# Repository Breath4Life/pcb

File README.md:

# Electronic circuit description

In this repository you will find the design files for hardware electronic design for the Breath4Life project.
Supported CAD software:
- Eagle

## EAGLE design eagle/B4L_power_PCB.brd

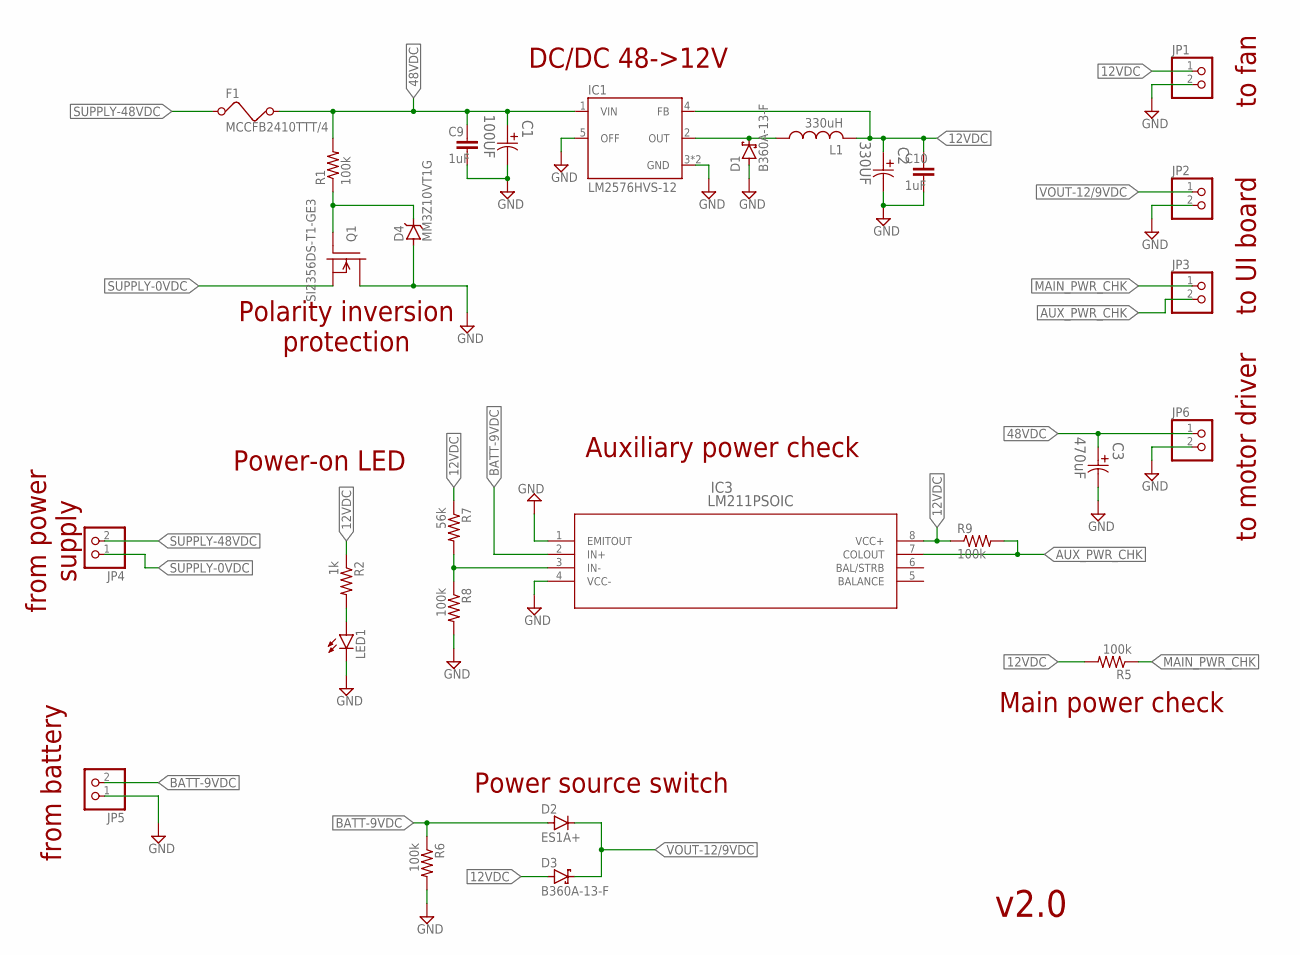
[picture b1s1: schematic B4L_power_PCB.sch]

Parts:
C1: 100UF; CAPAE1900X2200N
C2: 330UF; CAPAE830X1050N
C3: 470uF; CAPAE1900X1700N
C9: 1uF; C1206
C10: 1uF; C0603
D1, D3: B360A-13-F; DO214AC
D2: ES1A+; DO214AC
D4: MM3Z10VT1G; SOD323
F1: MCCFB2410TTT/4
IC1: LM2576HVS-12; TO263-5
IC3: LM211PSOIC; SO08
JP1, JP2, JP3, JP4, JP5, JP6: PINHD-1X2; 1X02
L1: 330uH; SRR1280A-331K
LED1: LED3MM
Q1: SI2356DS-T1-GE3; SOT23
R1, R5, R6, R8, R9: 100k; R0603
R2: 1k; R0603
R7: 56k; R0603

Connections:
12VDC: C2.1, C10.1, D3.A, IC1.4 (FB), IC3.8 (VCC+), JP1.1, L1.P$2 (2), R2.1, R5.2, R7.1, R9.1
48VDC: C1.1, C3.1, C9.1, F1.P$2 (2), IC1.1 (VIN), JP6.1, R1.2
AUX_PWR_CHK: IC3.7 (COLOUT), JP3.2, R9.2
BATT-9VDC: D2.A, IC3.2 (IN+), JP5.2, R6.1
GND: C1.2, C2.2, C3.2, C9.2, C10.2, D1.A, D4.2 (A), IC1.3 (GND), IC1.5 (OFF), IC1.6 (GND), IC3.1 (EMITOUT), IC3.4 (VCC-), JP1.2, JP2.2, JP5.1, JP6.2, LED1.K (C), Q1.3 (D), R6.2, R8.2
MAIN_PWR_CHK: JP3.1, R5.1
unnamed: D1.C, IC1.2 (OUT), L1.P$1 (1)
unnamed: D4.1 (C), Q1.1 (G), R1.1
unnamed: LED1.A, R2.2
unnamed: IC3.3 (IN-), R7.2, R8.1
SUPPLY-0VDC: JP4.1, Q1.2 (S)
SUPPLY-48VDC: F1.P$1 (1), JP4.2
VOUT-12/9VDC: D2.C, D3.C, JP2.1

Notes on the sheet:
v2.0
DC/DC 48->12V
Polarity inversion protection
Power source switch
to fan
Main power check
from battery
from power supply
Auxiliary power check
to UI board
to motor driver
Power-on LED

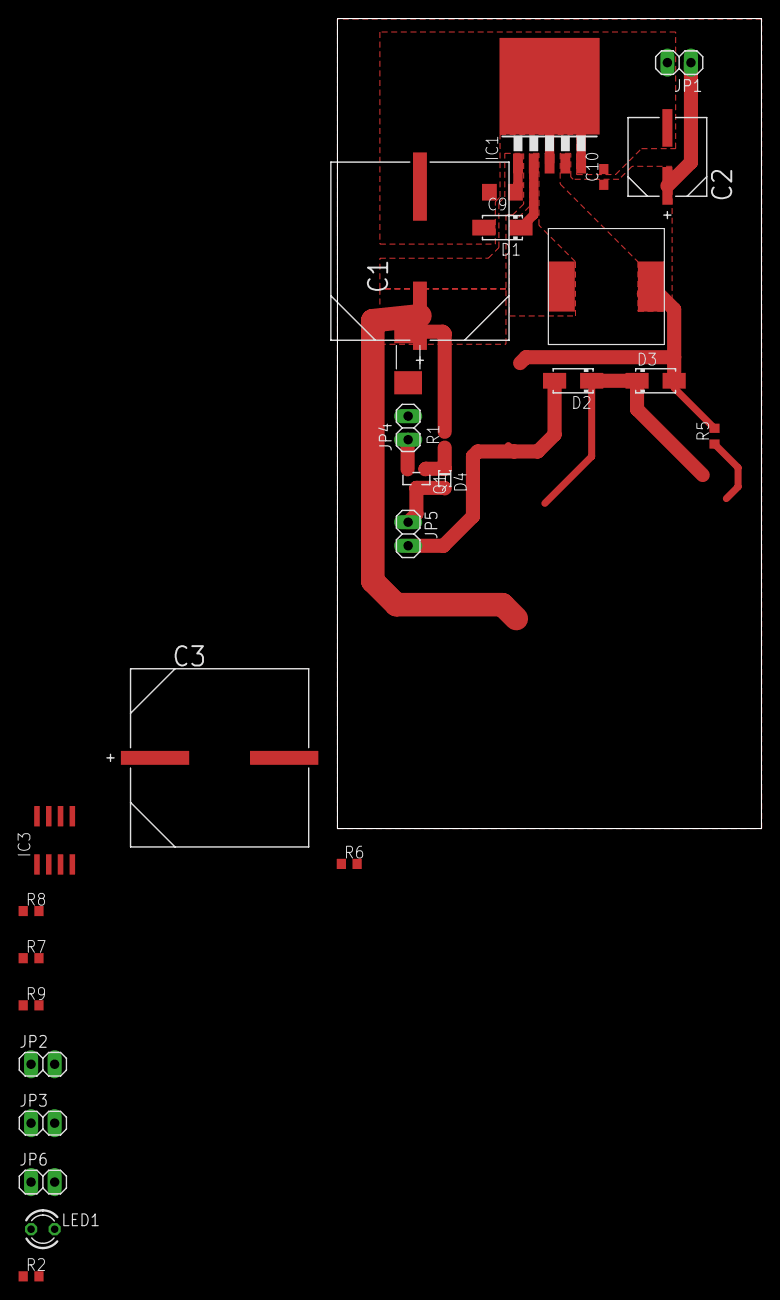
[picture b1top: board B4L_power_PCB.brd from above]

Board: 2 copper layers, 45.7 x 87.3 mm, 28 parts (0 on the bottom side), 13 nets.

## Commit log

2020-03-30 Add gitignore
2020-03-30 Add power board
2020-03-30 Add UI board (pin mapping not OK)
2020-03-31 Update UI, correct pin mapping
2020-03-31 Duplicate UART (for TX/RX on arduino)
2020-04-03 start v2 PCB design
2020-04-03 finish initial routing
2020-04-15 Power board update to 48V
2020-04-16 Update of LCD connectivity and capacitor values (near buttons)
2020-04-16 [UI board] Update of LEDs and resistors
2020-04-16 Create power board BOM
2020-04-16 [UI board] Addition of ACK button
2020-04-16 [UI board] Update of Arduino pin header connectivity
2020-04-16 Add schematic pdf
2020-04-16 Update PCB power for 48V supply
2020-04-19 [UI board] Update of buzzer driving circuit
2020-04-22 [UI board] Update of PDF version of the schematic
2020-04-22 Add motor, lim switch & flow sensor connexions to UI board
2020-04-22 update TODO
2020-04-22 Add value for capacitors
2020-04-23 [UI board] Correction of RBUZM resistor value
2020-04-23 add UI netlist
2020-04-28 [UI board] Correction of capacitors placement near the buttons
